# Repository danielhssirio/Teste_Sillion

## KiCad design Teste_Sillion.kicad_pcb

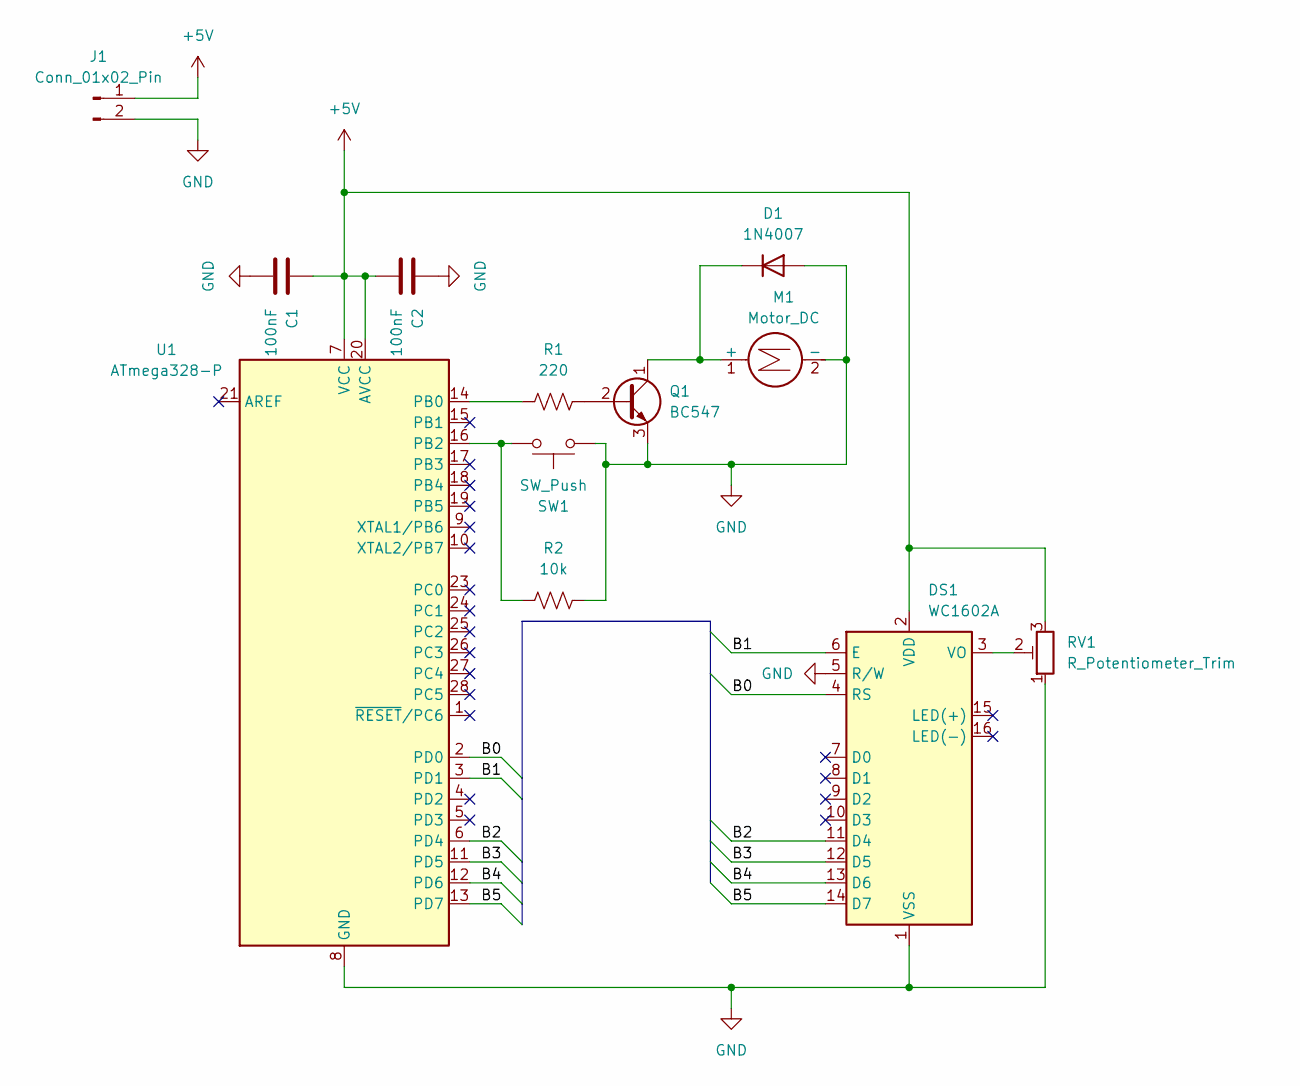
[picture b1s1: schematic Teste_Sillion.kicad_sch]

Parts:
C1, C2: 100nF; C_Radial_D4.0mm_H5.0mm_P1.50mm
D1: 1N4007; D_DO-41_SOD81_P10.16mm_Horizontal
DS1: WC1602A
J1: Conn_01x02_Pin; Molex_KK-254_AE-6410-02A_1x02_P2.54mm_Vertical
M1: Motor_DC; PinHeader_1x02_P2.54mm_Horizontal
Q1: BC547; TO-92_Inline
R1: 220; R_1206_3216Metric
R2: 10k; R_1206_3216Metric
RV1: R_Potentiometer_Trim; Potentiometer_ACP_CA6-VSMD_Vertical
SW1: SW_Push; SW_Push_1P1T_NO_CK_PTS125Sx43PSMTR
U1: ATmega328-P; DIP-28_W7.62mm

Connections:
+5V: C1.1, C2.2, DS1.2 (VDD), J1.1, RV1.3, U1.7 (VCC), U1.20 (AVCC)
/B0: DS1.4 (RS), U1.2 (PD0)
/B1: DS1.6 (E), U1.3 (PD1)
/B2: DS1.11 (D4), U1.6 (PD4)
/B3: DS1.12 (D5), U1.11 (PD5)
/B4: DS1.13 (D6), U1.12 (PD6)
/B5: DS1.14 (D7), U1.13 (PD7)
GND: C1.2, C2.1, D1.2 (A), DS1.1 (VSS), DS1.5 (R/W), J1.2, M1.2 (-), Q1.3 (E), R2.2, RV1.1, SW1.1, U1.8 (GND), U1.22 (GND)
unnamed: D1.1 (K), M1.1 (+), Q1.1 (C)
unnamed: DS1.3 (VO), RV1.2
unnamed: Q1.2 (B), R1.2
unnamed: R1.1, U1.14 (PB0)
unnamed: R2.1, SW1.2, U1.16 (PB2)

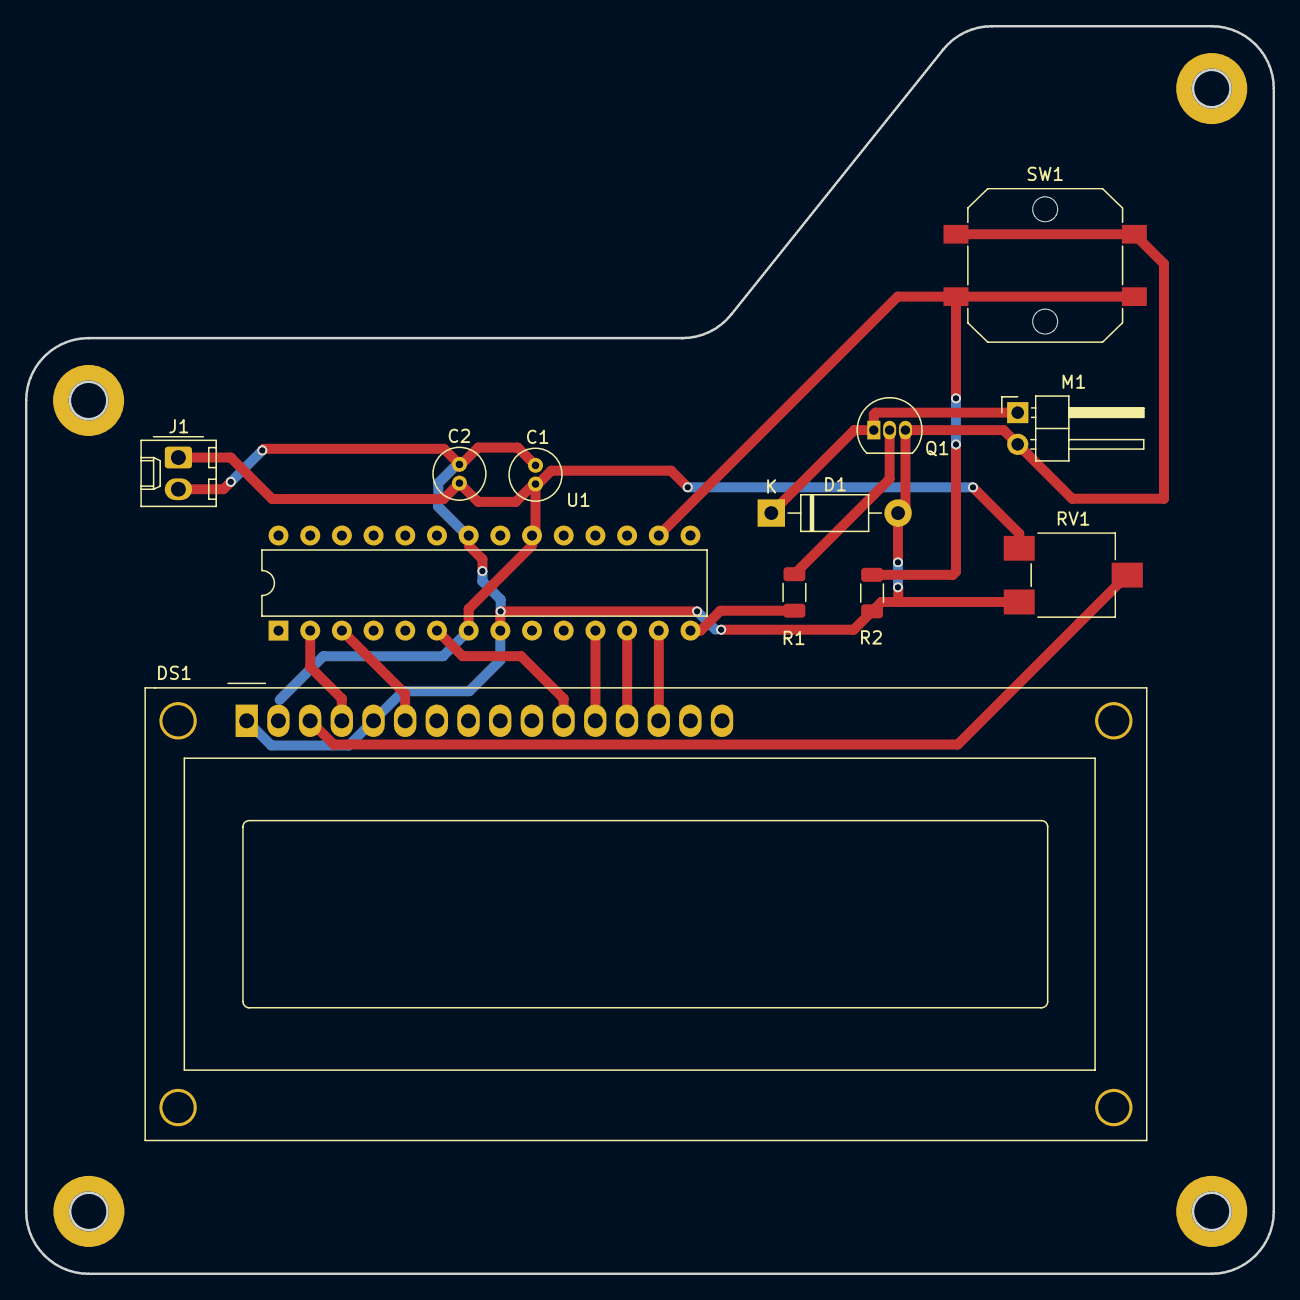
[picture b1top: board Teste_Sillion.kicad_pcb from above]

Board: 2 copper layers, 100.0 x 100.0 mm, 12 parts (0 on the bottom side), 13 nets.

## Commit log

2024-10-16 Adicionando pasta do projeto ao Repositório
2024-10-16 Atualizando Repositório
